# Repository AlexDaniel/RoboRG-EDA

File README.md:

# RoboRG-EDA

Schematics and PCB design files.

## License

    RoboRG is a low-cost camera motion control system.
    Copyright © 2018-2019
        Aleks-Daniel Jakimenko-Aleksejev <alex.jakimenko@gmail.com>

    This program is free software: you can redistribute it and/or modify
    it under the terms of the GNU Affero General Public License as
    published by the Free Software Foundation, either version 3 of the
    License, or (at your option) any later version.

    This program is distributed in the hope that it will be useful,
    but WITHOUT ANY WARRANTY; without even the implied warranty of
    MERCHANTABILITY or FITNESS FOR A PARTICULAR PURPOSE.  See the
    GNU Affero General Public License for more details.

    You should have received a copy of the GNU Affero General Public License
    along with this program.  If not, see <https://www.gnu.org/licenses/>.

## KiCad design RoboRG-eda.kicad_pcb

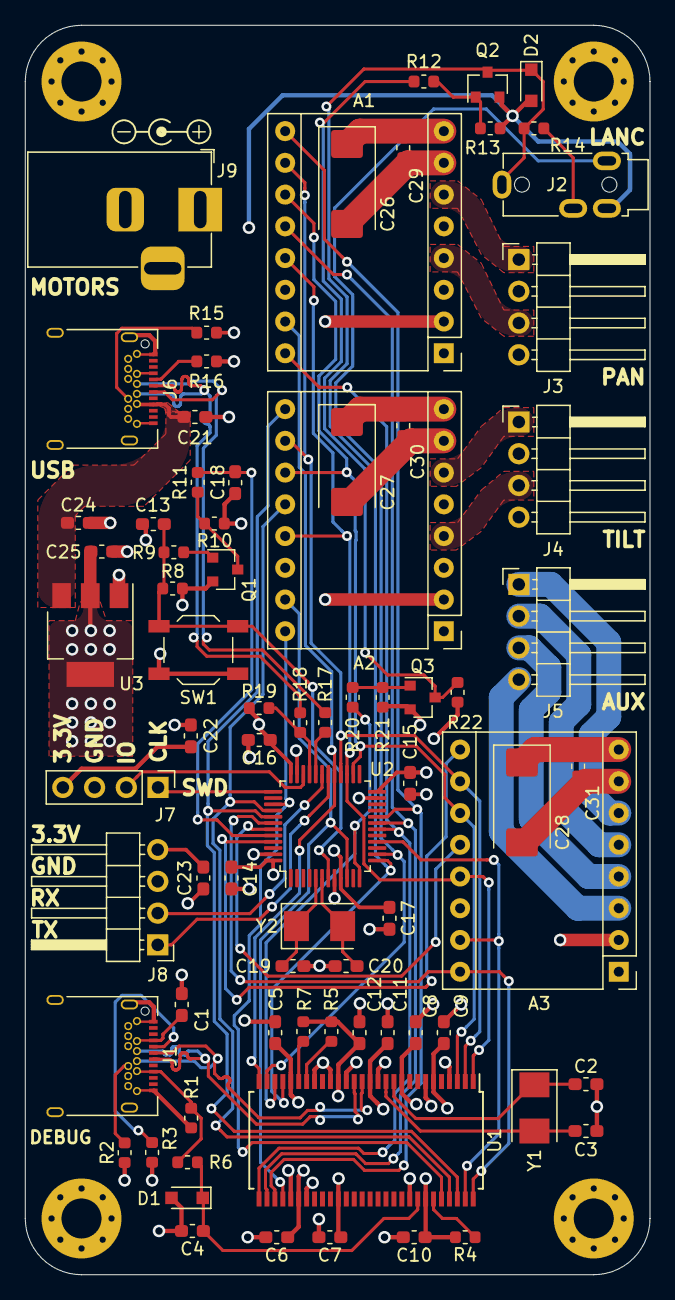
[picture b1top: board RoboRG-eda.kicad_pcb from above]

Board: 4 copper layers, 50.0 x 100.0 mm, 80 parts (0 on the bottom side), 65 nets.

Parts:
A1: driver-pan (TMC2130); Pololu_Breakout-16_15.2x20.3mm
A2: driver-tilt (TMC2130); Pololu_Breakout-16_15.2x20.3mm
A3: driver-other (TMC2130); Pololu_Breakout-16_15.2x20.3mm
C1, C4, C5, C6, C7, C8, C9, C10, C11, C12, C13, C14, C15, C16, C17, C21, C22, C23, C24, C29, C30, C31: 100nF; C_0603_1608Metric_Pad1.05x0.95mm_HandSolder
C2, C3, C19, C20: 16pF; C_0603_1608Metric_Pad1.05x0.95mm_HandSolder
C18: 4.7µF; C_0603_1608Metric_Pad1.05x0.95mm_HandSolder
C25: 10µF; C_0603_1608Metric_Pad1.05x0.95mm_HandSolder
C26, C27, C28: 33µF; CP_EIA-7343-31_Kemet-D_Pad2.25x2.55mm_HandSolder
D1, D2: 3.3V; D_SOD-323_HandSoldering
H1, H2, H3, H4: MountingHole_Pad; MountingHole_3.2mm_M3_Pad_Via
J1, J6: USB_C_Receptacle_USB2.0; USB_C_Receptacle_Amphenol_12401548E4-2A
J2: AudioJack3_Switch; Jack_2.5mm_PJ-218A-SMT_Horizontal
J3: connector-pan; PinHeader_1x04_P2.54mm_Horizontal
J4: connector-tilt; PinHeader_1x04_P2.54mm_Horizontal
J5: connector-other; PinHeader_1x04_P2.54mm_Horizontal
J7: SWD; PinHeader_1x04_P2.54mm_Vertical
J8: USART; PinHeader_1x04_P2.54mm_Horizontal
J9: Barrel_Jack_Switch; BarrelJack_Horizontal
Q1: Q_PNP_BEC; SOT-23
Q2, Q3: Q_NPN_BEC; SOT-23
R1, R6, R9, R12, R20, R22: 1kΩ; R_0603_1608Metric
R2, R3, R15, R16: 5.1kΩ; R_0603_1608Metric
R4, R5, R7: 4.7kΩ; R_0603_1608Metric
R8, R10, R13, R21: 10kΩ; R_0603_1608Metric
R11: 33kΩ; R_0603_1608Metric
R14: 4.7KΩ; R_0603_1608Metric
R17, R18: 22Ω; R_0603_1608Metric
R19: 1.5kΩ; R_0603_1608Metric
SW1: SW_Push; SW_SPST_TL3342
U1: CY7C68013A-56PVX; SSOP-56_7.5x18.5mm_P0.635mm
U2: STM32F103C8Tx; LQFP-48_7x7mm_P0.5mm
U3: LD1117S33TR_SOT223; SOT-223-3_TabPin2
Y1: 24MHz; Crystal_SMD_5032-2Pin_5.0x3.2mm
Y2: 8MHz; Crystal_SMD_5032-2Pin_5.0x3.2mm

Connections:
+3V3: A1.2, A2.2, A3.2, C5.1, C6.1, C7.1, C8.1, C9.1, C10.1, C11.1, C12.1, C14.1, C15.1, C16.1, C17.1, C22.1, C23.1, C25.1, J7.4, J8.4, Q1.2, R4.1, R5.1, R7.1, R8.1, R19.1, R22.1, U1.6, U1.10, U1.14, U1.18, U1.24, U1.34, U1.39, U1.50, U2.9, U2.24, U2.36, U2.48, U3.2
+5V: C21.1, C24.1, J6.A4, J6.A9, J6.B4, J6.B9, U3.3
/Connections/SWD-CLK: J7.1, U2.37
/Connections/SWD-IO: J7.2, U2.34
/Connections/USART-RX: J8.2, U2.31
/Connections/USART-TX: J8.1, U2.30
/Connections/USB-D+: R18.1, R19.2, U2.33
/Connections/USB-D-: R17.1, U2.32
/Connections/USB-MCU-D+: J6.A6, J6.B6, R18.2
/Connections/USB-MCU-D-: J6.A7, J6.B7, R17.2
/Drivers/1A-other: A3.4, J5.3
/Drivers/1A-pan: A1.4, J3.3
/Drivers/1A-tilt: A2.4, J4.3
/Drivers/1B-other: A3.3, J5.4
/Drivers/1B-pan: A1.3, J3.4
/Drivers/1B-tilt: A2.3, J4.4
/Drivers/2A-other: A3.5, J5.2
/Drivers/2A-pan: A1.5, J3.2
/Drivers/2A-tilt: A2.5, J4.2
/Drivers/2B-other: A3.6, J5.1
/Drivers/2B-pan: A1.6, J3.1
/Drivers/2B-tilt: A2.6, J4.1
/Optional/5V-LA: C1.1, J1.A4, J1.A9, J1.B4, J1.B9, R1.1, R6.1
/Optional/USB-LA-D+: J1.A6, J1.B6, U1.15
/Optional/USB-LA-D-: J1.A7, J1.B7, U1.16
BOOT0: C18.1, R11.2, U2.44
GND: A1.1, A1.7, A2.1, A2.7, A3.1, A3.7, C1.2, C2.2, C3.2, C4.2, C5.2, C6.2, C7.2, C8.2, C9.2, C10.2, C11.2, C12.2, C13.2, C14.2, C15.2, C16.2, C17.2, C18.2, C19.2, C20.2, C21.2, C22.2, C23.2, C24.2, C25.2, C26.2, C27.2, C28.2, C29.2, C30.2, C31.2, D1.2, D2.2, H1.1, H2.1, H3.1, H4.1, J1.A1, J1.A12, J1.B1, J1.B12, J1.S1, J2.S, J6.A1, J6.A12, J6.B1, J6.B12, J6.S1, J7.3, J8.3, J9.2, J9.3, Q2.2, Q3.2, R1.2, R2.2, R3.2, R10.2, R13.2, R15.2, R16.2, R21.2, SW1.2, U1.4, U1.7, U1.13, U1.17, U1.19, U1.21, U1.33, U1.35, U1.48, U2.8, U2.23, U2.35, U2.47, U3.1
LANC-detect: J2.SN, U1.27, U2.14
LANC-in: D2.1, J2.T, Q2.3, R14.2, U1.25, U2.13
LANC-out: R20.2, U1.26, U2.12
NRST: C13.1, R8.2, R9.2, SW1.1, U2.7
unnamed: C2.1, U1.11, Y1.1
unnamed: C3.1, U1.12, Y1.2
unnamed: C4.1, D1.1, R6.2, U1.49
unnamed: C19.1, U2.5, Y2.1
unnamed: C20.1, U2.6, Y2.2
unnamed: J1.A5, R3.1
unnamed: J1.B5, R2.1
unnamed: J2.R, R14.1
unnamed: J6.A5, R16.1
unnamed: J6.B5, R15.1
unnamed: Q1.1, R9.1
unnamed: Q1.3, R10.1, R11.1
unnamed: Q2.1, R12.1, R13.1
unnamed: Q3.1, R20.1, R21.1
unnamed: Q3.3, R12.2, R22.2
unnamed: R4.2, U1.51
unnamed: R5.2, U1.22
unnamed: R7.2, U1.23
SPI-MISO: A1.13, A2.13, A3.13, U1.1, U2.27
SPI-MOSI: A1.10, A2.10, A3.10, U1.2, U2.28
SPI-SCK: A1.11, A2.11, A3.11, U1.3, U2.26
VDC: A1.8, A2.8, A3.8, C26.1, C27.1, C28.1, C29.1, C30.1, C31.1, J9.1
dir-other: A3.16, U1.56, U2.42
dir-pan: A1.16, U1.29, U2.18
dir-tilt: A2.16, U1.52, U2.39
enable-other: A3.9, U2.45
enable-pan: A1.9, U1.31, U2.20
enable-tilt: A2.9, U1.54, U2.41
select-other: A3.12, U2.43
select-pan: A1.12, U1.30, U2.19
select-tilt: A2.12, U1.53, U2.40
step-other: A3.15, U1.55, U2.16
step-pan: A1.15, U1.28, U2.29
step-tilt: A2.15, U1.32, U2.10

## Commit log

2019-05-10 First revision with all files
    The edit history is not quite there, but hopefully from now on all
    changes will be versioned.
2019-05-11 Fix step/dir connections for AUX driver
    They were reversed.
2019-05-11 Fix LANC pinout
    Ring and tip were reversed.
2019-05-12 Add inverter on LANC-out
    So that it is possible to use hardware UART for pushing the bytes
    out. Note that it is known to be less reliable than bit-banging, but
    adding it anyway for completeness.
2019-05-13 Propagate all fixes to the PCB
    Also fix some footprints along the way.
2019-05-13 Proper page settings for the PCB
    Also bump the version to 1.0.1.
2019-05-16 Flip D+/D- of the LA
    Oops!
2019-05-16 Bump version
2019-05-17 Reorder sheets
    So that the PDF plot is nice.
2019-05-17 Make things more centered
2019-05-17 Fix version number on the silkscreen
2019-05-17 Tweak PDF generation
2019-05-21 Add an image to the README

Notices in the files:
RoboRG-eda.kicad_pcb:
Licensed under GNU AGPLv3 or any later version of the license
